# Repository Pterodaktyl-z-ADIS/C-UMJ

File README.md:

# Myszojeleń
Projekt robota typu Micromouse.

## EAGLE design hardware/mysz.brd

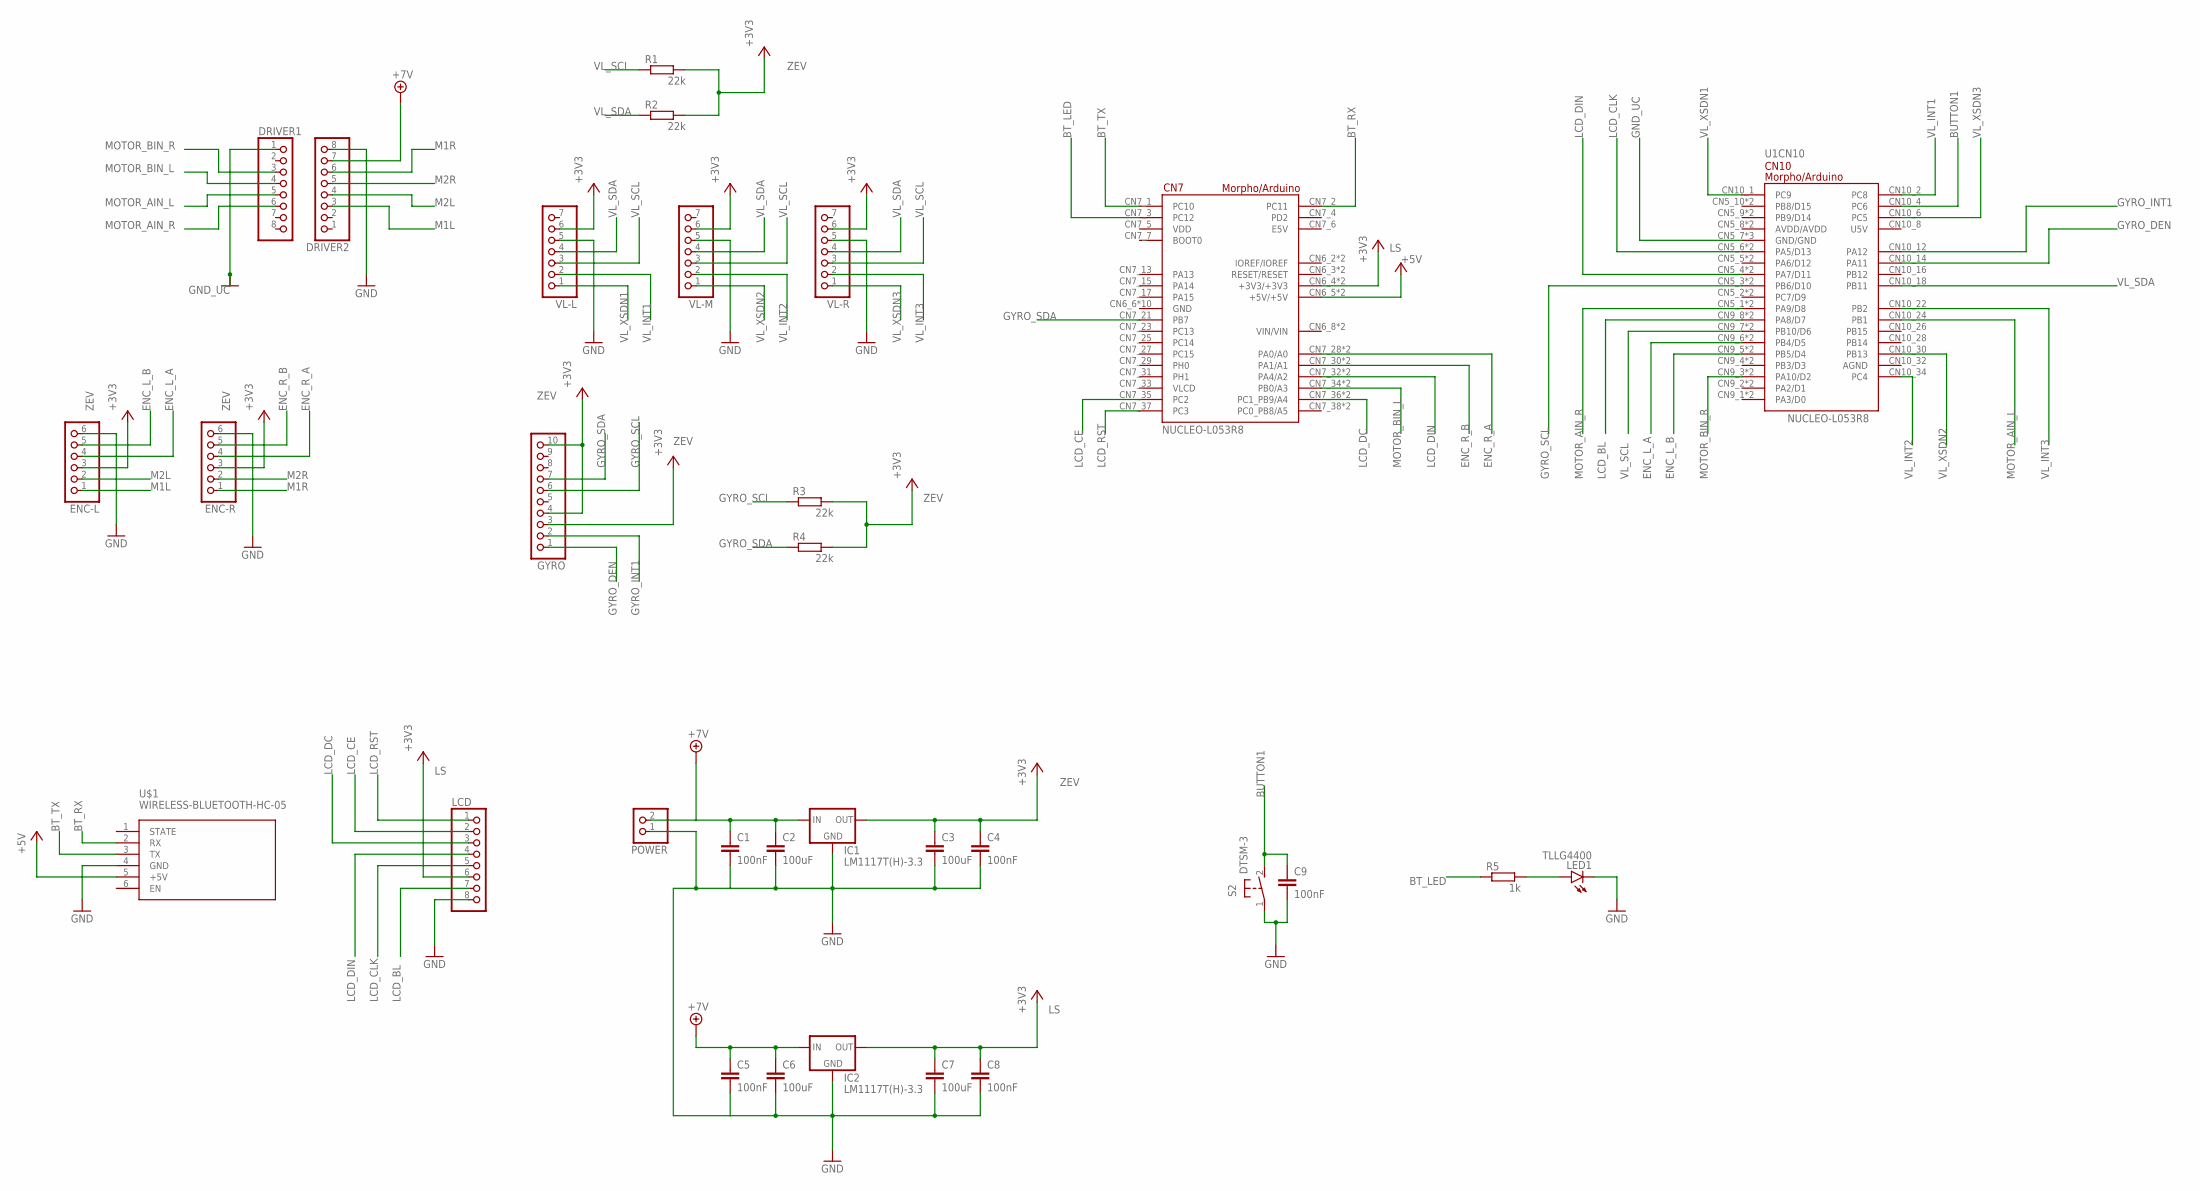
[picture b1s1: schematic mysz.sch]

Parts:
C1, C4, C5, C8, C9: 100nF; C2.5-3
C2, C3, C6, C7: 100uF; C2.5-3
DRIVER1, DRIVER2: PINHD-1X8; 1X08
ENC-L: PINHD-1X6; 1X06
ENC-R: PINHD-1X6; 1X06
GYRO: PINHD-1X10; 1X10
IC1, IC2: LM1117T(H)-3.3; TO220H
LCD: PINHD-1X8; 1X08
LED1: TLLG4400; LED3MM
POWER: PINHD-1X2; 1X02
R1, R2, R3, R4: 22k; 0207/10
R5: 1k; 0207/10
S2: DTSM-3
U1: NUCLEO-L053R8; MODULE_NUCLEO-L053R8
U$1: WIRELESS-BLUETOOTH-HC-05
VL-L: PINHD-1X7/90; 1X07/90
VL-M: PINHD-1X7/90; 1X07/90
VL-R: PINHD-1X7/90; 1X07/90

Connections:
+3V3: VL-L.6, VL-M.6, VL-R.6
+5V: U1.CN6_5 (+5V/+5V), U1.CN7_18 (+5V/+5V), U$1.5 (+5V)
+7V: C1.1, C2.1, C5.1, C6.1, IC1.3 (IN), IC2.3 (IN), POWER.2
BT_LED: R5.1, U1.CN7_3 (PC12)
BT_RX: U1.CN7_2 (PC11), U$1.2 (RX)
BT_TX: U1.CN7_1 (PC10), U$1.3 (TX)
BUTTON1: C9.1, S2.2, U1.CN10_4 (PC6)
ENC_L_A: ENC-L.4, U1.CN9_6 (PB4/D5), U1.CN10_27 (PB4/D5)
ENC_L_B: ENC-L.5, U1.CN9_5 (PB5/D4), U1.CN10_29 (PB5/D4)
ENC_R_A: ENC-R.4, U1.CN7_28 (PA0/A0), U1.CN8_1 (PA0/A0)
ENC_R_B: ENC-R.5, U1.CN7_30 (PA1/A1), U1.CN8_2 (PA1/A1)
GND: C1.2, C2.2, C3.2, C4.2, C5.2, C6.2, C7.2, C8.2, DRIVER2.8, ENC-L.6, ENC-R.6, IC1.1 (GND), IC2.1 (GND), LCD.8, POWER.1, U$1.4 (GND), VL-L.5, VL-M.5, VL-R.5
GND_UC: DRIVER1.1, U1.CN5_7 (GND/GND), U1.CN10_9 (GND/GND), U1.CN10_20 (GND/GND)
GYRO_DEN: GYRO.1, U1.CN10_14 (PA11)
GYRO_INT1: GYRO.2, U1.CN10_12 (PA12)
GYRO_SCL: GYRO.6, R3.1, U1.CN5_3 (PB6/D10), U1.CN10_17 (PB6/D10)
GYRO_SDA: GYRO.7, R4.1, U1.CN7_21 (PB7)
LCD_BL: LCD.7, U1.CN9_8 (PA8/D7), U1.CN10_23 (PA8/D7)
LCD_CE: LCD.2, U1.CN7_35 (PC2)
LCD_CLK: LCD.5, U1.CN5_6 (PA5/D13), U1.CN10_11 (PA5/D13)
LCD_DC: LCD.3, U1.CN7_36 (PC1_PB9/A4), U1.CN8_5 (PC1_PB9/A4)
LCD_DIN: LCD.4, U1.CN5_4 (PA7/D11), U1.CN7_32 (PA4/A2), U1.CN8_3 (PA4/A2), U1.CN10_15 (PA7/D11)
LCD_RST: LCD.1, U1.CN7_37 (PC3)
LS: C7.1, C8.1, IC2.2 (OUT), LCD.6, U1.CN6_4 (+3V3/+3V3), U1.CN7_16 (+3V3/+3V3)
M1L: DRIVER2.3, ENC-L.1
M1R: DRIVER2.6, ENC-R.1
M2L: DRIVER2.4, ENC-L.2
M2R: DRIVER2.5, ENC-R.2
MOTOR_AIN_L: DRIVER1.5, U1.CN10_24 (PB1)
MOTOR_AIN_R: DRIVER1.6, U1.CN5_1 (PA9/D8), U1.CN10_21 (PA9/D8)
MOTOR_BIN_L: DRIVER1.4, U1.CN7_34 (PB0/A3), U1.CN8_4 (PB0/A3)
MOTOR_BIN_R: DRIVER1.3, U1.CN9_3 (PA10/D2), U1.CN10_33 (PA10/D2)
unnamed: C9.2, LED1.K (C), S2.1
unnamed: LED1.A, R5.2
VL_INT1: U1.CN10_2 (PC8), VL-L.2
VL_INT2: U1.CN10_34 (PC4), VL-M.2
VL_INT3: U1.CN10_22 (PB2), VL-R.2
VL_SCL: R1.1, U1.CN9_7 (PB10/D6), U1.CN10_25 (PB10/D6), VL-L.3, VL-M.3, VL-R.3
VL_SDA: R2.1, U1.CN10_18 (PB11), VL-L.4, VL-M.4, VL-R.4
VL_XSDN1: U1.CN10_1 (PC9), VL-L.1
VL_XSDN2: U1.CN10_30 (PB13), VL-M.1
VL_XSDN3: U1.CN10_6 (PC5), VL-R.1
ZEV: C3.1, C4.1, ENC-L.3, ENC-R.3, GYRO.3, GYRO.4, GYRO.10, IC1.2 (OUT), R1.2, R2.2, R3.2, R4.2

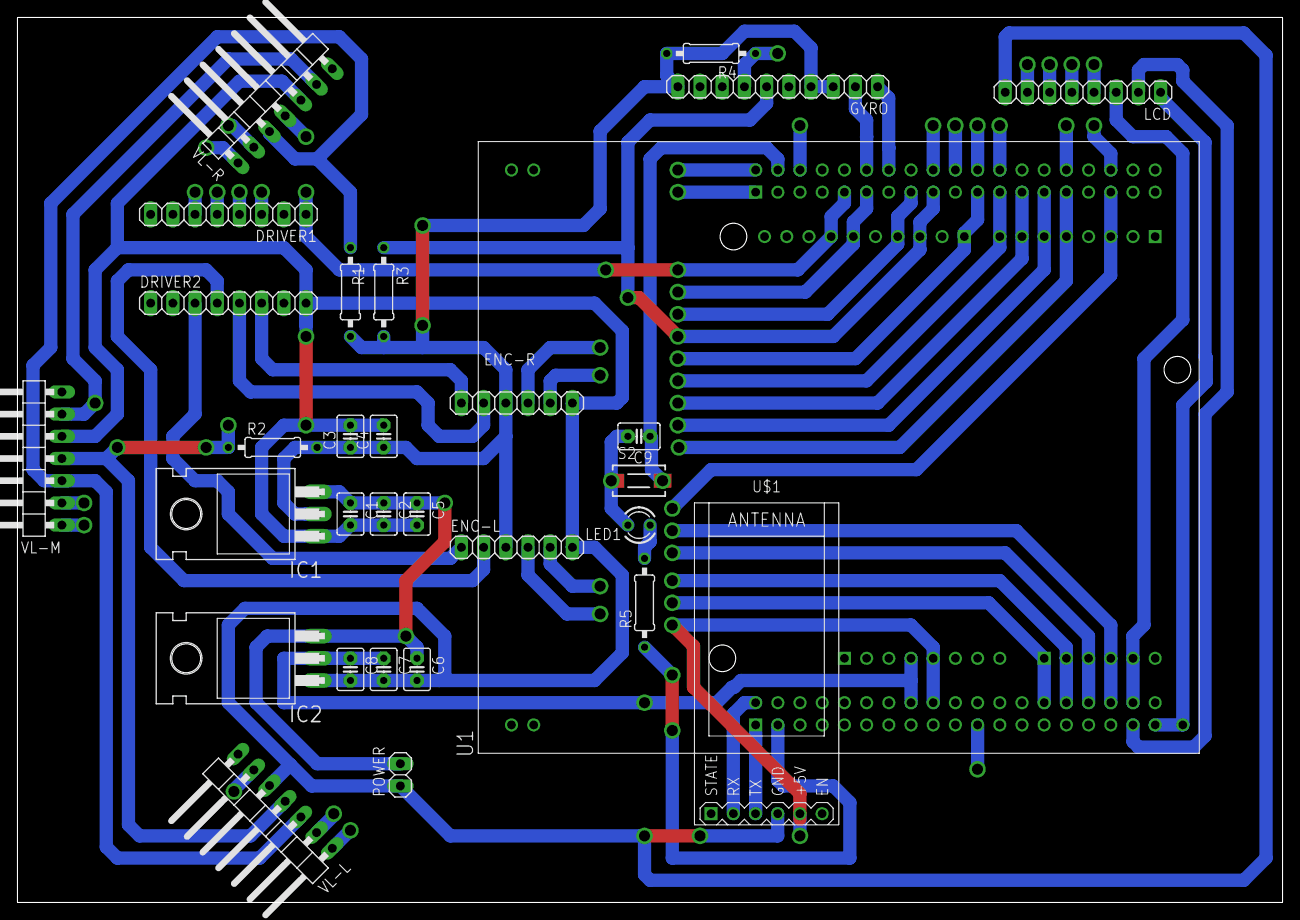
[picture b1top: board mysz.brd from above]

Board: 2 copper layers, 144.8 x 101.3 mm, 30 parts (0 on the bottom side), 43 nets.

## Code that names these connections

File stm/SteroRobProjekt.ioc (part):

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Mcu.Name=STM32F103R(8-B)Tx
Mcu.Package=LQFP64
Mcu.UserName=STM32F103RBTx
PA0-WKUP.GPIOParameters=GPIO_Label
PA0-WKUP.GPIO_Label=ENC_R_A
PA0-WKUP.Signal=S_TIM2_CH1_ETR
PA1.GPIOParameters=GPIO_Label
PA1.GPIO_Label=ENC_R_B
PA1.Signal=S_TIM2_CH2
PA10.GPIOParameters=GPIO_Label
PA10.GPIO_Label=MOTOR_BIN_R
PA10.Signal=S_TIM1_CH3
PA11.GPIOParameters=GPIO_Label
PA11.GPIO_Label=GYRO_DEN
PA11.Signal=GPIO_Input
PA12.GPIOParameters=GPIO_Label
PA12.GPIO_Label=GYRO_INT1
PA12.Signal=GPIO_Input
PA13.Mode=Serial_Wire
PA13.Signal=SYS_JTMS-SWDIO
PA14.Mode=Serial_Wire
PA14.Signal=SYS_JTCK-SWCLK
PA5.GPIOParameters=GPIO_Label
PA5.GPIO_Label=LCD_CLK
PA5.Mode=TX_Only_Simplex_Unidirect_Master
PA5.Signal=SPI1_SCK
PA7.GPIOParameters=GPIO_Label
PA7.GPIO_Label=LCD_DIN
PA7.Mode=TX_Only_Simplex_Unidirect_Master
PA7.Signal=SPI1_MOSI
PA8.GPIOParameters=GPIO_Label
PA8.GPIO_Label=LCD_BL
PA8.Signal=GPIO_Output
PA9.GPIOParameters=GPIO_Label
PA9.GPIO_Label=MOTOR_AIN_R
PA9.Signal=S_TIM1_CH2
PB0.GPIOParameters=GPIO_Label
PB0.GPIO_Label=MOTOR_BIN_L
PB0.Signal=S_TIM3_CH3
PB1.GPIOParameters=GPIO_Label
PB1.GPIO_Label=MOTOR_AIN_L
PB1.Signal=S_TIM3_CH4
PB10.GPIOParameters=GPIO_Label
PB10.GPIO_Label=VL_SCL
PB10.Mode=I2C
PB10.Signal=I2C2_SCL
PB11.GPIOParameters=GPIO_Label
PB11.GPIO_Label=VL_SDA
PB11.Mode=I2C
PB11.Signal=I2C2_SDA
PB13.GPIOParameters=GPIO_Label
PB13.GPIO_Label=VL_XSDN2
PB13.Signal=GPIO_Output
PB2.GPIOParameters=GPIO_Label
PB2.GPIO_Label=VL_INT3
PB2.Signal=GPXTI2
PB4.GPIOParameters=GPIO_Label
PB4.GPIO_Label=ENC_L_A
PB4.Signal=S_TIM3_CH1
PB5.GPIOParameters=GPIO_Label
PB5.GPIO_Label=ENC_L_B
PB5.Signal=S_TIM3_CH2
PB6.GPIOParameters=GPIO_Label
PB6.GPIO_Label=GYRO_SCL
PB6.Mode=I2C
PB6.Signal=I2C1_SCL
PB7.GPIOParameters=GPIO_Label
PB7.GPIO_Label=GYRO_SDA
PB7.Mode=I2C
PB7.Signal=I2C1_SDA
PC0.GPIOParameters=GPIO_Label
PC0.GPIO_Label=BATTERY
PC0.Signal=ADCx_IN10
PC1.GPIOParameters=GPIO_Label
PC1.GPIO_Label=LCD_DC
PC1.Signal=GPIO_Output
PC10.GPIOParameters=GPIO_Label
PC10.GPIO_Label=BT_TX
PC10.Mode=Asynchronous
PC10.Signal=USART3_TX
PC11.GPIOParameters=GPIO_Label
PC11.GPIO_Label=BT_RX
PC11.Mode=Asynchronous
PC11.Signal=USART3_RX
PC12.GPIOParameters=GPIO_Label
PC12.GPIO_Label=BT_LED
PC12.Signal=GPIO_Input
PC2.GPIOParameters=GPIO_Label
PC2.GPIO_Label=LCD_CE
PC2.Signal=GPIO_Output
PC3.GPIOParameters=GPIO_Label
PC3.GPIO_Label=LCD_RST
PC3.Signal=GPIO_Output
PC4.GPIOParameters=GPIO_Label
PC4.GPIO_Label=VL_INT2
PC4.Signal=GPXTI4
PC5.GPIOParameters=GPIO_Label
PC5.GPIO_Label=VL_XSDN3
PC5.Signal=GPIO_Output
PC6.GPIOParameters=GPIO_Label
PC6.GPIO_Label=BUTTON1
PC6.Signal=GPIO_Input
PC8.GPIOParameters=GPIO_Label
PC8.GPIO_Label=VL_INT1
PC8.Signal=GPXTI8
PC9.GPIOParameters=GPIO_Label
PC9.GPIO_Label=VL_XSDN1
PC9.Signal=GPIO_Output
PD0-OSC_IN.Mode=HSE-External-Oscillator
PD0-OSC_IN.Signal=RCC_OSC_IN
PD1-OSC_OUT.Mode=HSE-External-Oscillator
PD1-OSC_OUT.Signal=RCC_OSC_OUT
RCC.SYSCLKFreq_VALUE=64000000
RCC.SYSCLKSource=RCC_SYSCLKSOURCE_PLLCLK
board=NUCLEO-F103RB

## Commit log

2020-04-17 Wall Follower Algorythm
2020-04-25 Repo create
2020-04-25 Hardware add
2020-04-25 Rm eagle file
2020-04-27 Add Gyro schemat
2020-04-28 Add driver
2020-04-30 gitignore update
2020-04-30 STM32 project init
2020-04-30 conection models to stm & stm corected
2020-05-01 finished hardware & stm I2C problem
2020-05-02 Labirynth class
2020-05-02 Position.h class
2020-05-02 Sensors.h class
2020-05-02 Main file
    empty for now
2020-05-02 Wall follow algorythm
    Not completed yet
2020-05-06 Main project files and 3D in progress
2020-05-06 WDS init & schem finished
2020-05-08 Adjusted wires.brd
2020-05-08 Adjusted wires.sch
2020-05-08 Added missing links.sch
2020-05-08 Added dimensions.brd
2020-05-08 switched capacitor
2020-05-08 board setup
2020-05-08 Board finished
2020-05-08 Updated dim.brd
2020-05-08 made groups
2020-05-09 Added sensors, move class, finished alg.
2020-05-11 improved board
2020-05-12 Project file
2020-05-13 tcp connection - disconection not working
2020-05-13 Added class for OGL widget
2020-05-13 Added
2020-05-14 Mouse model & display
2020-05-14 Mouse object
2020-05-15 pdf files
2020-05-16 better print 1.0

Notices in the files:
parts and their libraries:
diy-modules: Released under the Creative Commons Attribution 4.0 International License: http://creativecommons.org/licenses/by/4.0
